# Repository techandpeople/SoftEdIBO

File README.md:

# SoftEdIBO

Soft-based robot platform for inclusive, embodied interaction.
Developed at [LASIGE](https://www.lasige.pt/), Faculdade de Ciencias, Universidade de Lisboa.

SoftEdIBO controls soft robots equipped with inflatable air chambers.
Participants interact by touching the robots, which respond through inflation and deflation.
The system supports multiple robot types (Turtle, Tree, Thymio) and activity modes.

> **Running a study?** See [SETUP.md](SETUP.md) for skin/sensor setup, magnet
> polarity, touch calibration, and the gesture-training workflow.

---

## Hardware requirements

| Component | Quantity | Notes |
|-----------|----------|-------|
| Seeed XIAO ESP32-S3 (gateway) | 1 | Connected to PC via USB; also runs a WiFi SoftAP (WiFi-OTA) + a UART link to a companion XIAO ESP32-C6 for dongle-free Thymio control |
| Seeed XIAO ESP32-C6 (Thymio RCP) | 0-1 | Optional - impersonates the Thymio RF dongle over 802.15.4 (drive wheels/LEDs/sound, no dongle). See [docs/THYMIO_WIRELESS_CONTROL.md](docs/THYMIO_WIRELESS_CONTROL.md) |
| ESP32-WROOM-32 (`node_direct`) | 1 per direct board | 3 chambers, direct ADC sensors, onboard pumps |
| ESP32-WROOM-32 (`node_multiplexed`) | 1 per multiplexed board | Up to 9 chambers: 3 skins of 3, one pump pair each (runtime configurable) |
| DRV3297 motor driver | 1 (`node_direct`) / up to 3 (`node_multiplexed`) | Drives pumps with PWM |
| Air pump | 2 (`node_direct`) / up to 6 (`node_multiplexed`) | Inflate/deflate supply - pumps push directly into the chambers |
| XGZP6847A pressure sensor | 1 per chamber | Analog output (0-3.3 V) |
| Solenoid valves | 2 per chamber | Inflate + deflate via ULN2803A |

Flash the [gateway firmware](firmware/gateway/) to the USB-connected board - one
build, a **Seeed XIAO ESP32-S3** (ESP-IDF), which does everything: ESP-NOW chamber
control + a WiFi SoftAP (for WiFi-OTA) + a UART link to a companion C6 for Thymios.
For each node, choose the matching firmware target:

| Firmware | Path | When to use |
|----------|------|-------------|
| `node_actuator` env `direct` / `direct_debug` | [firmware/node_actuator/](firmware/node_actuator/) | Direct board (fixed 3 chambers) |
| `node_actuator` env `multiplexed` / `multiplexed_debug` | [firmware/node_actuator/](firmware/node_actuator/) | Multiplexed board (default 9 chambers, runtime configurable) |
| `node_magnet_sensor` | [firmware/node_magnet_sensor/](firmware/node_magnet_sensor/) | 4x MLX90393 magnetic touch board (`node_magnet_sensor` protocol) |

---

## Architecture

```
PC --USB--> Gateway (XIAO ESP32-S3) --ESP-NOW--> node_direct      (3 chambers, direct GPIO valves + own pumps)
                                    |        +-> node_multiplexed (up to 9 chambers)
                                    +--UART--> C6 --802.15.4--> Thymio  (dongle-free wheels/LEDs/sound; optional)
```

**Software layers:**

```
SessionPanel
  +-- Activity (declarative behaviours run by ScriptedActivity)
        +-- Robot (Turtle / Tree / Thymio / Simulated)
              +-- Node(s)  (ESP32, identified by MAC + node_type + max_slots)
              +-- Skin(s)  (logical grouping of 1-3 chambers from one node of this robot)
                    +-- AirChamber  (local index 0-2, pressure 0-100 %)
```

- **Node** is a physical ESP32. Its `node_type` (`node_direct` or `node_multiplexed`) determines which firmware to flash.
- **Skin** groups 1-3 chambers, all on the same node (a skin never spans MACs). Activities address chambers by local skin index (0, 1, 2) - no knowledge of node topology required.
- **Pressure** is expressed as **0-100 %** of the maximum pressure configured on each node.
- **Per-chamber max pressure** is set in `settings.yaml` and enforced both in the app and on the ESP32 (hardware safety - survives app crashes).
- **Pressure sensing** uses the XGZP6847A datasheet transfer function (see [pressure.h](firmware/common/pressure.h)).

**Touch sensing (optional).** A skin may reference a `node_magnet_sensor` (4-sensor magnet sensor/touch board) via its `touch:` block - see [firmware/PROTOCOL.md](firmware/PROTOCOL.md). The activity-time view (`SkinGridView`) overlays a pulsing yellow outline on the active sensor cells so the operator sees where each touch lands relative to the chamber regions.

**Skin geometry by type.** Each skin sets a `skin_type` (e.g. `turtle_square`, `tree_round`, `thymio`) whose **shape and sensor coordinates** are hardcoded in [`src/hardware/skin_geometry.py`](src/hardware/skin_geometry.py). The skin dialog offers only the current robot's types and draws the real outline/aspect (square, rectangle, round, triangle, Thymio "D") - editor and activity view share the masks in [`src/gui/skin_shapes.py`](src/gui/skin_shapes.py). The legacy paint-grid editor still applies to skins without a `skin_type`.

**Sensor stream recording + touch-gesture ML.** A session can record every sensor message to `data/recordings/<id>.jsonl` (toggle in the setup dialog - no video). Those recordings, plus gestures tagged live in the observer panel, feed a **per-`skin_type`, coordinate-free** touch-gesture classifier (tap / press / compressions - `src/ml/gesture_taxonomy.py`). `scikit-learn` is the optional `ml` extra; the classifier is inert without a trained model. See [docs/TOUCH_ML.md](docs/TOUCH_ML.md).

**Activities are declarative behaviours.** No activities are hard-coded: every activity is a behaviour spec authored in the block editor (**Tools -> Activity Editor...**), stored in the DB (or imported from JSON examples in `config/examples/behaviours/`) and interpreted at session time by `ScriptedActivity`. See [docs/ACTIVITIES.md](docs/ACTIVITIES.md).

---

## Installation

### Linux (x86-64)

```bash
curl -fsSL https://raw.githubusercontent.com/techandpeople/SoftEdIBO/master/install.sh | bash
```

This will download the latest release, install it to `~/.local/opt/SoftEdIBO/`, create a `softedibo` command in `~/.local/bin/`, and add a desktop entry to the application menu.

**Nightly build** (latest commit on `master`):

```bash
curl -fsSL https://raw.githubusercontent.com/techandpeople/SoftEdIBO/master/install.sh | bash -s -- --nightly
```

**Uninstall:**

```bash
softedibo --uninstall
```

> **First time with USB?** After installing, run:
> ```bash
> sudo usermod -aG dialout $USER
> ```
> Then log out and back in. The installer does this automatically if needed.

---

### Windows (x64)

1. Download **`SoftEdIBO-windows-x64.zip`** from the [latest release](https://github.com/techandpeople/SoftEdIBO/releases/latest)
2. Extract and run **`SoftEdIBO.exe`**

> **USB driver:** install the [CH340](https://www.wch-ic.com/downloads/CH341SER_EXE.html) or [CP210x](https://www.silabs.com/developers/usb-to-uart-bridge-vcp-drivers) driver if your device is not detected.

---

## Usage

On first launch, a setup wizard guides you through flashing the firmware to the ESP32 nodes.

### Configuration (`settings.yaml`)

The app reads and writes the **user copy** of the settings file:
`~/.local/share/SoftEdIBO/config/settings.yaml` on Linux,
`%APPDATA%\SoftEdIBO\config\settings.yaml` on Windows. On first run it is copied
from the bundled default, the repo's [config/settings.yaml](config/settings.yaml);
later edits to the repo file do not reach an existing user copy.

Robots are configured per type (`turtles:` / `trees:` / `thymios:`), each with its own `nodes:` (ESP32s by MAC) and `skins:` on top. A skin lists its chambers - each a `{mac, slot}` pair on a single node - with optional per-chamber `max_pressure` / `min_pressure` safety limits in kPa. It is all editable from the GUI (Robots panel); the commented examples in [config/settings.yaml](config/settings.yaml) show the full shape (skin types, touch blocks, Thymio entries).

```yaml
robots:
  turtles:
    - id: turtle_1
      nodes:
        - mac: "AA:BB:CC:DD:EE:01"
          node_type: "node_multiplexed"
          max_slots: 12
      skins:
        - skin_id: shell_top
          name: Shell Top
          skin_type: turtle_square
          chambers:
            - {mac: "AA:BB:CC:DD:EE:01", slot: 0, max_pressure: 8.0}
            - {mac: "AA:BB:CC:DD:EE:01", slot: 1, max_pressure: 6.0}
  trees: []
  thymios: []
```

- Multiple skins can share the same node MAC; each skin groups up to 3 of that node's slots.
- `max_pressure` is sent to the ESP32 node on startup as kPa. The gateway forwards it unchanged; the node enforces it independently - even if the app crashes, chambers will not exceed their configured limit.
- If `max_pressure` / `min_pressure` are omitted, chambers default to 30 kPa / -5 kPa.

---

## Development

### Python application

```bash
# Qt platform libs (Debian/Ubuntu). Without libxcb-cursor0 the app aborts with
# "Could not load the Qt platform plugin xcb" - the app forces xcb (see run.py).
# libxkbfile1 is needed by QtWebEngine (the activity editor crashes without it).
sudo apt-get install -y libgl1 libegl1 libglib2.0-0 libdbus-1-3 \
  libxcb1 libxcb-cursor0 libxcb-icccm4 libxcb-image0 libxcb-keysyms1 \
  libxcb-randr0 libxcb-render-util0 libxcb-shape0 libxcb-xinerama0 \
  libxcb-xkb1 libxkbcommon-x11-0 libfontconfig1 libxkbfile1

git clone https://github.com/techandpeople/SoftEdIBO.git
cd SoftEdIBO
python -m venv .venv && source .venv/bin/activate
pip install -r requirements.txt
./scripts/compile_ui.sh     # generates src/gui/ui_*.py - not in git
python scripts/run.py
```

Or with the Makefile: `make install && make run` (`make` alone lists every
target - tests, type check, firmware build/flash/monitor, PyInstaller bundle).
`make run` recompiles only the changed `.ui` files on its own.

Requires Python 3.12+. Re-run `./scripts/compile_ui.sh` after editing any
`src/gui/ui/*.ui` file, or the app fails with
`ModuleNotFoundError: No module named 'src.gui.ui_...'`.

**Debug mode** - shows all log levels on the console (DEBUG+):

```bash
python scripts/run.py --debug
```

Without `--debug`, only warnings and errors are shown on the console. All log
levels are always written to `softedibo.log` in the per-user state directory
(`~/.local/state/SoftEdIBO/` on Linux, `%LOCALAPPDATA%\SoftEdIBO\` on Windows;
rotating, 2 MB x 3 backups).

### Firmware

```bash
# Gateway - one build, Seeed XIAO ESP32-S3 (ESP-IDF)
cd firmware/gateway && pio run -e seeed_xiao_esp32s3 --target upload

# Actuator nodes (one project, env per variant)
cd firmware/node_actuator && pio run -e direct      --target upload
cd firmware/node_actuator && pio run -e multiplexed --target upload

# Sensor node (4x MLX90393 touch board)
cd firmware/node_magnet_sensor && pio run -e release --target upload

# Thymio radio co-processor (optional) - Seeed XIAO ESP32-C6
cd firmware/thymio_rcp && pio run -e rcp_c6 --target upload
```

Prebuilt binaries for all of the above are produced by `scripts/build-firmware.sh`.

Requires [PlatformIO](https://platformio.org/).

> **Updating nodes later:** once a node has been cable-flashed once with the
> current partition table, you can reflash it wirelessly via **Tools -> Update
> Nodes (OTA)...** in the app - it streams the bundled firmware to the node over
> ESP-NOW through the connected gateway (no cable, no WiFi). See
> [firmware/gateway/README.md](firmware/gateway/README.md#ota-firmware-update-over-esp-now).

CI builds **every** firmware variant on each run (release + debug, RGB + RGBW)
and ships them all - bundled in the app and in `firmware.zip` - for both the
nightly pre-release (push to `master`) and stable releases (tag `v*`). The debug
build is picked at flash time with the **Debug build** checkbox in the setup
wizard / **Tools -> Update Nodes (OTA)...**.

### Debug builds

| Layer | Production | Development |
|-------|-----------|-------------|
| **Python app** | `run.py` - warnings only on console | `run.py --debug` - all levels on console |
| **Node firmware** | `release` env - no Serial, no debug overhead | `debug` env - Serial logs, tx counters, `{"cmd":"debug"}` |
| **Gateway firmware** | Single build, no debug overhead | Same (transparent bridge, nothing to gate) |

### Key source paths

| Path | Description |
|------|-------------|
| `src/hardware/skin.py` | Skin model - groups 1-3 AirChambers on one ESP32 node; `skin_type` + `geometry` |
| `src/hardware/skin_geometry.py` | Hardcoded skin-geometry registry (shape + sensor coords) keyed by `skin_type` |
| `src/hardware/air_chamber.py` | AirChamber model - pressure 0-100 %, configurable max |
| `src/hardware/esp32_controller.py` | Real hardware controller (via the SoftEdIBO gateway) |
| `src/hardware/simulated_controller.py` | Mock controller for simulation mode |
| `src/hardware/touch_profiles.py` | Touch-sensor technology seam (magnet today, capacitive skeleton) - see [docs/TOUCH_SENSORS.md](docs/TOUCH_SENSORS.md) |
| `src/data/stream_recorder.py` | Per-session JSONL recorder of all gateway sensor messages |
| `src/data/export.py` | Session CSV export with robot/participant attribution |
| `src/ml/` | Touch-gesture pipeline (segmenter, features, classifier) - see [docs/TOUCH_ML.md](docs/TOUCH_ML.md) |
| `src/gui/skin_shapes.py` | Shared skin-outline masks (round/triangle/thymio) + aspect ratio |
| `src/robots/` | TurtleRobot, TreeRobot, ThymioRobot, SimulatedRobot |
| `src/activities/` | Activity registry + declarative behaviour engine (`ScriptedActivity`, verb catalogue) |
| `src/gui/monitor/` | Live pressure monitor widgets |
| `scripts/label_touches.py` / `scripts/train_touch_model.py` | Offline touch-gesture labelling + training (`.[ml]` extra) |
| `src/log.py` | Centralized logging setup (console + rotating file) |
| `config/settings.yaml` | Default robot and hardware configuration (copied to the user data dir on first run) |
| `firmware/gateway/` | Gateway firmware (ESP-IDF, Seeed XIAO ESP32-S3) |
| `firmware/thymio_rcp/` | Thymio radio co-processor (XIAO ESP32-C6) - dongle-free 802.15.4 control; see [docs/THYMIO_WIRELESS_CONTROL.md](docs/THYMIO_WIRELESS_CONTROL.md) |
| `firmware/common/` | Shared firmware headers (`se_espnow.h`, units/pressure/dbg/cmd_queue) |
| `firmware/node_actuator/` | Actuator nodes - `direct` + `multiplexed` variants (build-flag envs) |
| `firmware/node_magnet_sensor/` | Sensor node - 4x MLX90393 touch board (`node_magnet_sensor` protocol) |
| `firmware/node_actuator/src/direct/pins.h` | node_direct pin definitions |
| `firmware/node_actuator/src/multiplexed/pins.h` | node_multiplexed pin definitions |

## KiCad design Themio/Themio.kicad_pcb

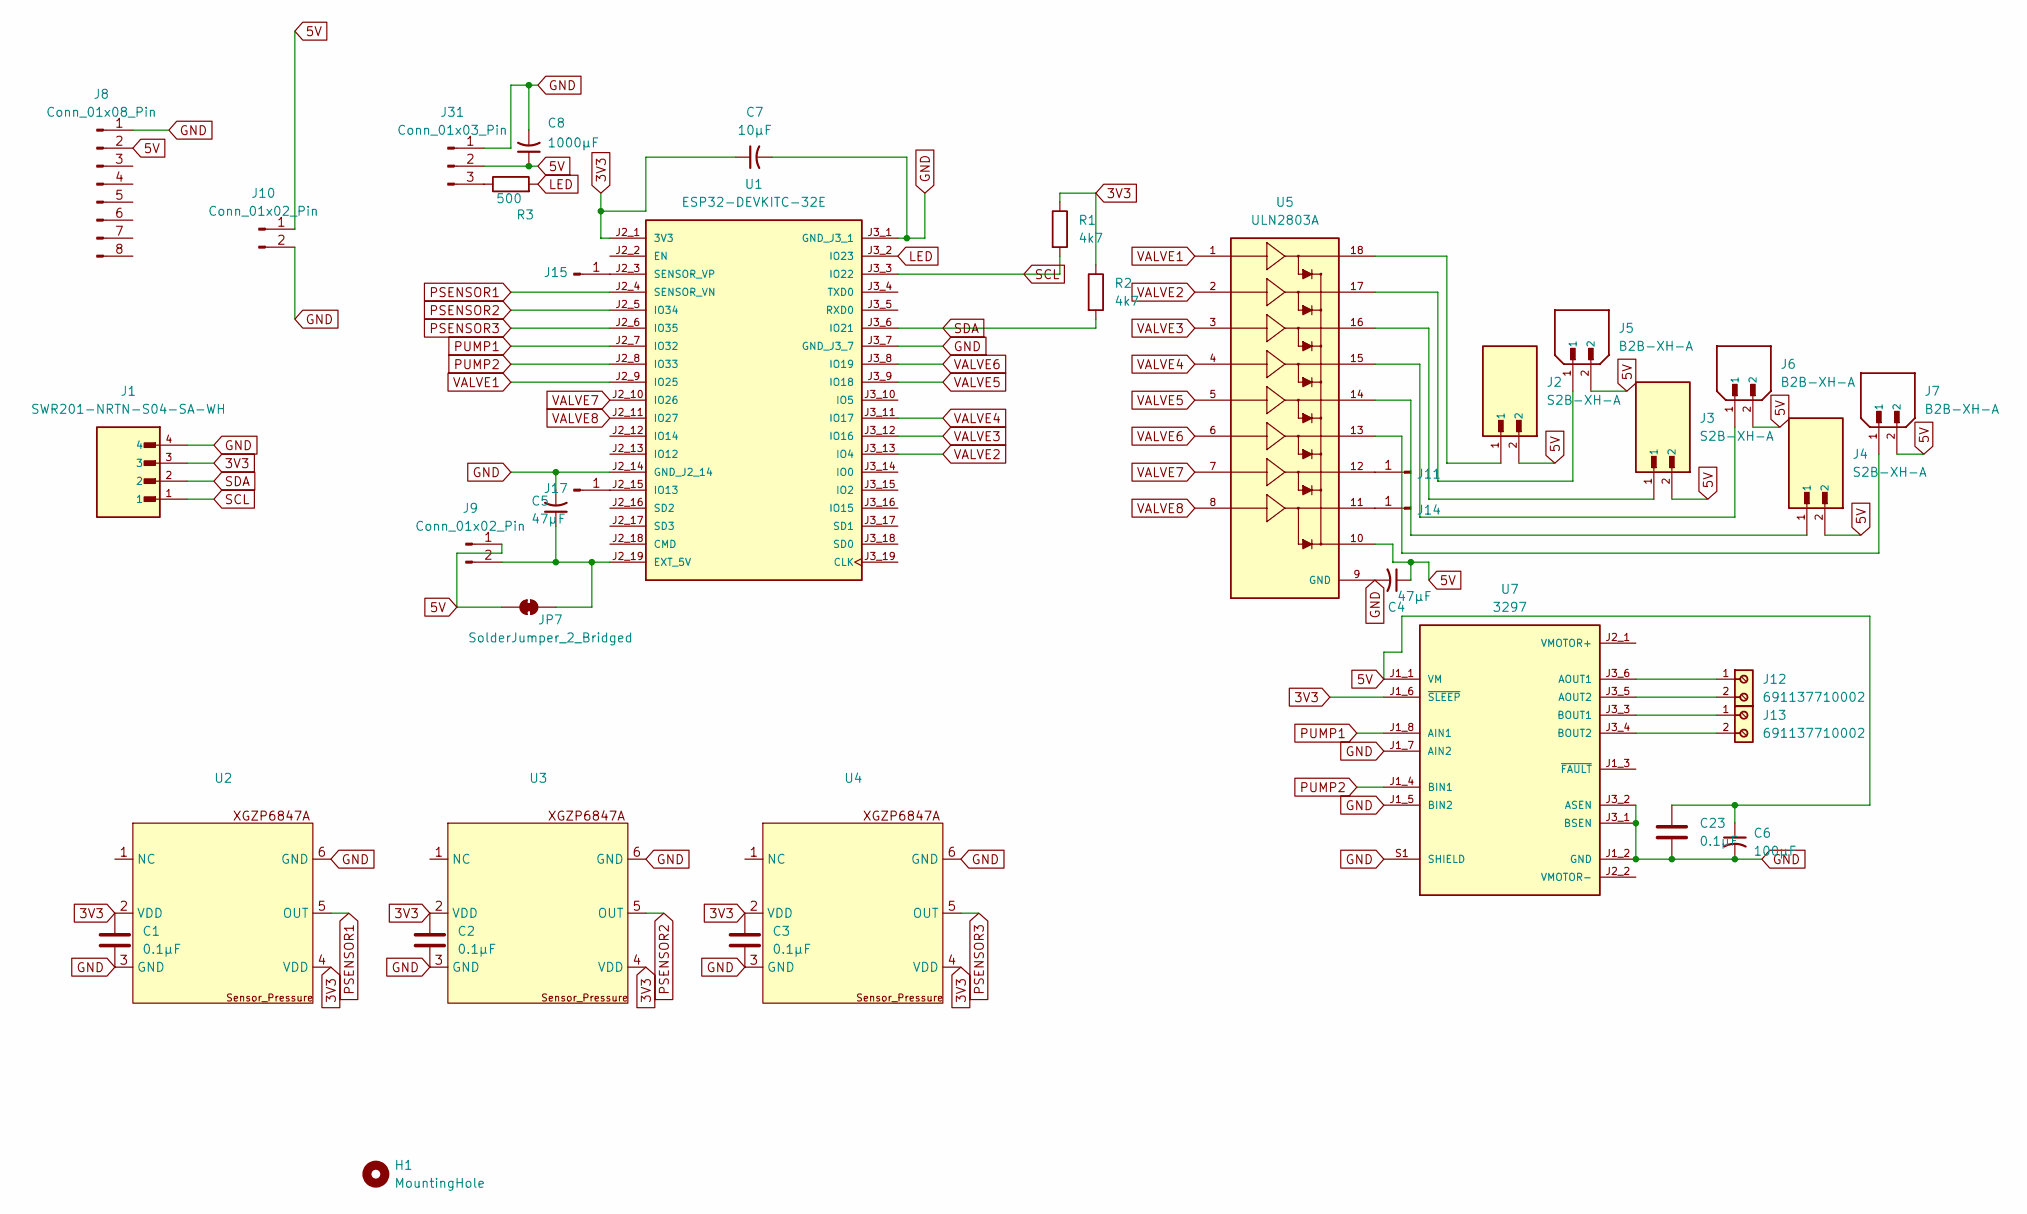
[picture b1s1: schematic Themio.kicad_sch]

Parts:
C1, C2, C3, C23: 0.1µF; C_Disc_D5.0mm_W2.5mm_P5.00mm
C4, C5: 47µF; CP_Radial_D5.0mm_P2.00mm
C6: 100µF; CP_Radial_D5.0mm_P2.00mm
C7: 10µF; CP_Radial_D5.0mm_P2.00mm
C8: 1000µF; CP_Radial_D5.0mm_P2.00mm
H1: MountingHole; MountingHole_4.3mm_M4
J1: SWR201-NRTN-S04-SA-WH; SULLINS_SWR201-NRTN-S04-SA-WH; PARTREV A
J2, J3, J4: S2B-XH-A; JST_S2B-XH-A
J5, J6, J7: B2B-XH-A; JST_B2B-XH-A; PARTREV N/A
J8: Conn_01x08_Pin; PinHeader_1x08_P2.54mm_Vertical
J9, J10: Conn_01x02_Pin; PinHeader_1x02_P2.54mm_Vertical
J11, J14, J15, J17: Conn_01x01_Pin; PinHeader_1x01_P2.54mm_Vertical
J12, J13: 691137710002
J31: Conn_01x03_Pin; PinHeader_1x03_P2.54mm_Vertical
JP7: SolderJumper_2_Bridged; SolderJumper-2_P1.3mm_Bridged_RoundedPad1.0x1.5mm
R1, R2: 4k7; R_Axial_DIN0207_L6.3mm_D2.5mm_P7.62mm_Horizontal
R3: 500; R_Axial_DIN0207_L6.3mm_D2.5mm_P7.62mm_Horizontal
U1: ESP32-DEVKITC-32E; MODULE_ESP32-DEVKITC-32E; PARTREV 1.4
U2, U3, U4: XGP6847A_TiagoDias
U5: ULN2803A; UNL; PARTREV 4
U7: 3297; MODULE_3297; PARTREV 2020-11-20

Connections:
3V3: C1.1, C2.1, C3.1, C7.1, J1.3, R1.1, R2.1, U1.J2_1 (3V3), U2.2 (VDD), U2.4 (VDD), U3.2 (VDD), U3.4 (VDD), U4.2 (VDD), U4.4 (VDD), U7.J1_6 (~SLEEP)
5V: C4.1, C6.1, C8.1, C23.1, J2.2, J3.2, J4.2, J5.2, J6.2, J7.2, J8.2, J9.1, J10.1, J31.2, JP7.1 (A), U5.10, U7.J1_1 (VM)
GND: C1.2, C2.2, C3.2, C4.2, C5.2, C6.2, C7.2, C8.2, C23.2, J1.4, J8.1, J10.2, J31.1, U1.J2_14 (GND_J2_14), U1.J3_1 (GND_J3_1), U1.J3_7 (GND_J3_7), U2.3 (GND), U2.6 (GND), U3.3 (GND), U3.6 (GND), U4.3 (GND), U4.6 (GND), U5.9 (GND), U7.J1_2 (GND), U7.J1_5 (BIN2), U7.J1_7 (AIN2), U7.J3_1 (BSEN), U7.J3_2 (ASEN), U7.S1 (SHIELD), U7.S2 (SHIELD)
LED: R3.2, U1.J3_2 (IO23)
unnamed: J2.1, U5.18
unnamed: J3.1, U5.16
unnamed: J4.1, U5.14
unnamed: J5.1, U5.17
unnamed: J6.1, U5.15
unnamed: J7.1, U5.13
unnamed: C5.1, J9.2, JP7.2 (B), U1.J2_19 (EXT_5V)
unnamed: J11.1, U5.12
unnamed: J14.1, U5.11
unnamed: J15.1, U1.J2_3 (SENSOR_VP)
unnamed: J17.1, U1.J2_15 (IO13)
unnamed: J31.3, R3.1
unnamed: J12.1, U7.J3_6 (AOUT1)
unnamed: J12.2, U7.J3_5 (AOUT2)
unnamed: J13.1, U7.J3_3 (BOUT1)
unnamed: J13.2, U7.J3_4 (BOUT2)
PSENSOR1: U1.J2_4 (SENSOR_VN), U2.5 (OUT)
PSENSOR2: U1.J2_5 (IO34), U3.5 (OUT)
PSENSOR3: U1.J2_6 (IO35), U4.5 (OUT)
PUMP1: U1.J2_7 (IO32), U7.J1_8 (AIN1)
PUMP2: U1.J2_8 (IO33), U7.J1_4 (BIN1)
SCL: J1.1, R1.2, U1.J3_3 (IO22)
SDA: J1.2, R2.2, U1.J3_6 (IO21)
VALVE1: U1.J2_9 (IO25), U5.1
VALVE2: U1.J3_13 (IO4), U5.2
VALVE3: U1.J3_12 (IO16), U5.3
VALVE4: U1.J3_11 (IO17), U5.4
VALVE5: U1.J3_9 (IO18), U5.5
VALVE6: U1.J3_8 (IO19), U5.6
VALVE7: U1.J2_10 (IO26), U5.7
VALVE8: U1.J2_11 (IO27), U5.8

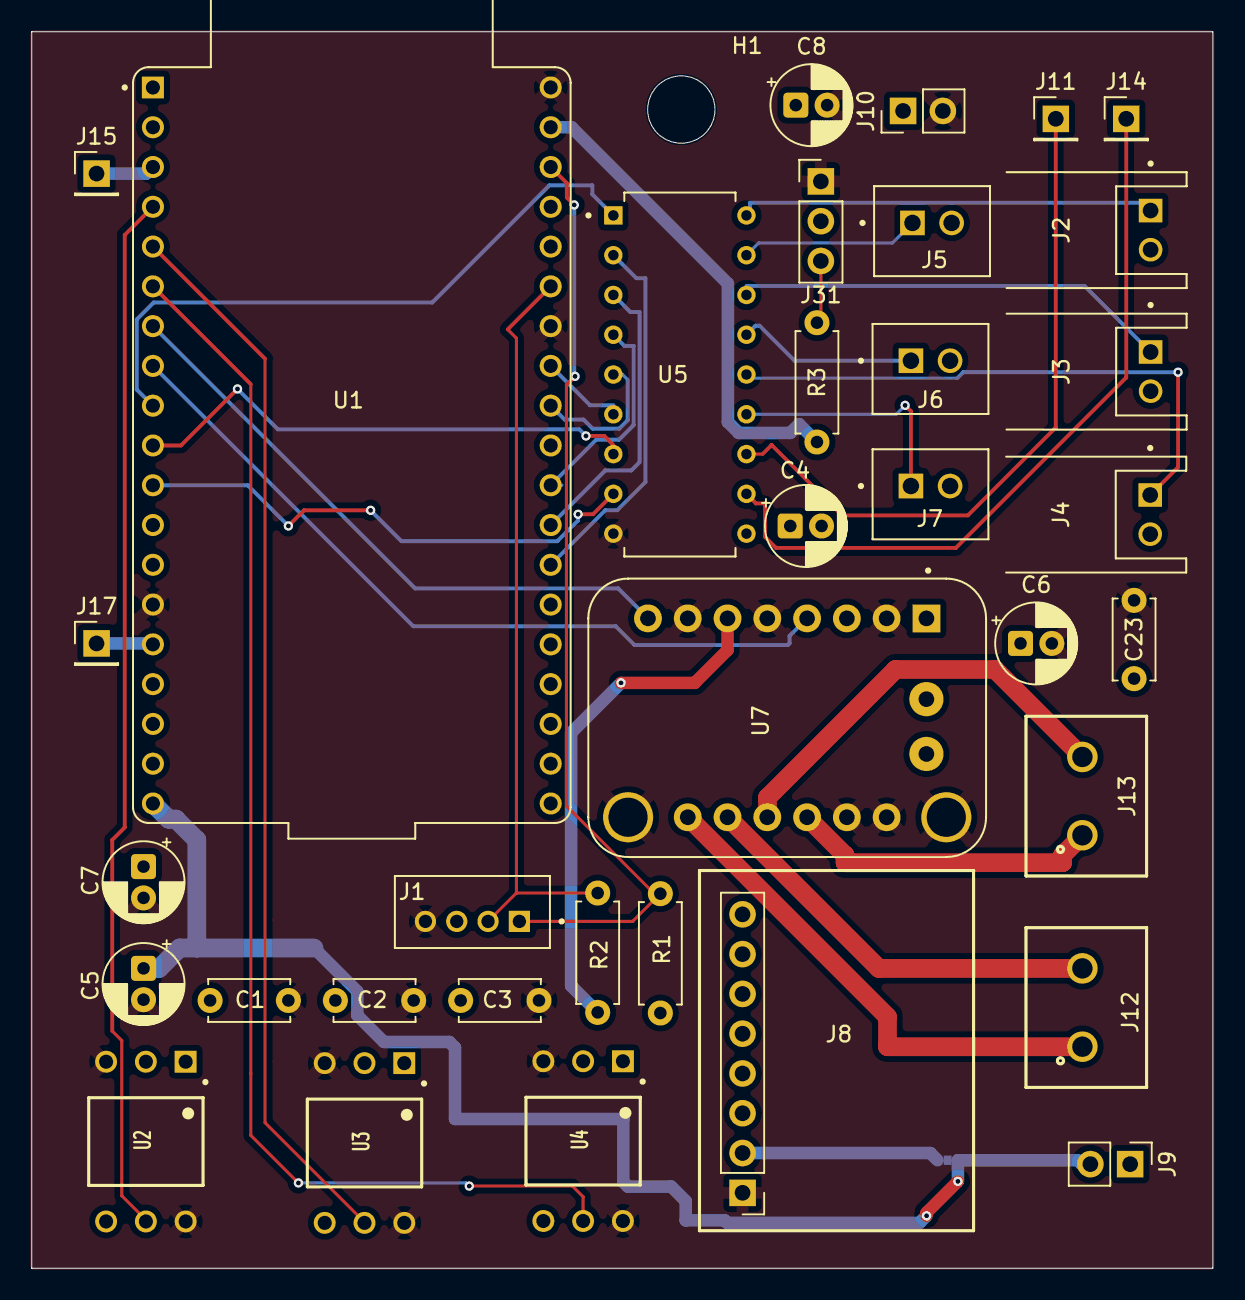
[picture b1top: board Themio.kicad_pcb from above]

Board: 4 copper layers, 75.4 x 79.0 mm, 37 parts (1 on the bottom side), 35 nets.

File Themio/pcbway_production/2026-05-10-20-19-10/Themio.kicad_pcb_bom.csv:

Designator,Quantity,Value,Footprint,Package,MPN,DNP,Mount_Type,Description,MF,MAXIMUM_PACKAGE_HEIGHT,Price,Check_prices,STANDARD,PARTREV,SnapEDA_Link,MP,Description_1,Availability,MANUFACTURER,Purchase-URL
"C1, C2, C23, C3",4,0.1µF,C_Disc_D5.0mm_W2.5mm_P5.00mm,,,,tht,Unpolarized capacitor,,,,,,,,,,,,
"C4, C5",2,47µF,CP_Radial_D5.0mm_P2.00mm,,,,tht,"capacitor, small US symbol",,,,,,,,,,,,
C6,1,100µF,CP_Radial_D5.0mm_P2.00mm,,,,tht,"capacitor, small US symbol",,,,,,,,,,,,
C7,1,10µF,CP_Radial_D5.0mm_P2.00mm,,,,tht,"capacitor, small US symbol",,,,,,,,,,,,
C8,1,1000µF,CP_Radial_D5.0mm_P2.00mm,,,,tht,"capacitor, small US symbol",,,,,,,,,,,,
J1,1,SWR201-NRTN-S04-SA-WH,SULLINS_SWR201-NRTN-S04-SA-WH,None,,,tht,,Sullins Connector Solutions,6.00mm,None,https://www.snapeda.com/parts/SWR201-NRTN-S04-SA-WH/Sullins/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,Manufacturer Recommendations,A,https://www.snapeda.com/parts/SWR201-NRTN-S04-SA-WH/Sullins/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,SWR201-NRTN-S04-SA-WH,Connector Header Through Hole 4 position 0.079 (2.00mm),In Stock,Sullins,
"J10, J9",2,Conn_01x02_Pin,PinHeader_1x02_P2.54mm_Vertical,,,,tht,"Generic connector, single row, 01x02, script generated",,,,,,,,,,,,
"J11, J14, J15, J17",4,Conn_01x01_Pin,PinHeader_1x01_P2.54mm_Vertical,,,,tht,"Generic connector, single row, 01x01, script generated",,,,,,,,,,,,
"J12, J13",2,691137710002,691137710002,None,,,tht,,Würth Elektronik,,None,https://www.snapeda.com/parts/691137710002/W%25C3%25BCrth+El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,,,https://www.snapeda.com/parts/691137710002/W%25C3%25BCrth+El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,691137710002,2 Position Wire to Board Terminal Block Horizontal with Board 0.197 (5.00mm) Through Hole,In Stock,,https://www.snapeda.com/api/url_track_click_mouser/?unipart_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 Elektronik&part_name=691137710002&search_term=691137710002
"J2, J3, J4",3,S2B-XH-A,JST_S2B-XH-A,None,,,tht,,JST Sales,,None,https://www.snapeda.com/parts/S2B-XH-A/JST/view-part/?ref=eda,,,https://www.snapeda.com/parts/S2B-XH-A/JST/view-part/?ref=snap,S2B-XH-A,"Connector Header Through Hole, Right Angle 2 position 0.098 (2.50mm)",In Stock,JST,https://www.snapeda.com/api/url_track_click_mouser/?unipart_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 Sales&part_name=S2B-XH-A&search_term=conector s2b-xh-a
J31,1,Conn_01x03_Pin,PinHeader_1x03_P2.54mm_Vertical,,,,tht,"Generic connector, single row, 01x03, script generated",,,,,,,,,,,,
"J5, J6, J7",3,B2B-XH-A,JST_B2B-XH-A,None,,,tht,,JST Sales,7 mm,None,https://www.snapeda.com/parts/B2B-XH-A/JST/view-part/?ref=eda,Manufacturer Recommendations,N/A,https://www.snapeda.com/parts/B2B-XH-A/JST/view-part/?ref=snap,B2B-XH-A,Connector Header Through Hole 2 position 0.098 (2.50mm),In Stock,JST Sales America Inc.,https://www.snapeda.com/api/url_track_click_mouser/?unipart_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 Sales&part_name=B2B-XH-A&search_term=b2b-xh-a
J8,1,Conn_01x08_Pin,PinHeader_1x08_P2.54mm_Vertical,,,,tht,"Generic connector, single row, 01x08, script generated",,,,,,,,,,,,
"R1, R2",2,4k7,R_Axial_DIN0207_L6.3mm_D2.5mm_P7.62mm_Horizontal,,,,tht,Resistor,,,,,,,,,,,,
R3,1,500,R_Axial_DIN0207_L6.3mm_D2.5mm_P7.62mm_Horizontal,,,,tht,Resistor,,,,,,,,,,,,
U1,1,ESP32-DEVKITC-32E,MODULE_ESP32-DEVKITC-32E,None,,,tht,,Espressif Systems,,None,https://www.snapeda.com/parts/ESP32-DEVKITC-32E/Espressif+Sy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,Manufacturer Recommendations,1.4,https://www.snapeda.com/parts/ESP32-DEVKITC-32E/Espressif+Sy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,ESP32-DEVKITC-32E,"The ESP32-DEVKITC-32E transceiver evaluation board from Espressif Systems is a powerful development tool for wireless communication technologies. It supports 802.11 b/g/n Wi-Fi and Bluetooth® Smart Ready 4.x (BLE) dual-mode at 2.4GHz, making it ideal for a variety of IoT applications. Equipped with a PCB antenna and 4MB flash, this board provides reliable connectivity and ample memory for developing and testing RF, RFID, and wireless solutions.",In Stock,Espressif Systems,https://www.snapeda.com/api/url_track_click_mouser/?unipart_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 Systems&part_name=ESP32-DEVKITC-32E&search_term=esp32
"U2, U3, U4",3,~,XGP6847A_TiagoDias,,,,tht,,,,,,,,,,,,,
U5,1,ULN2803A,UNL,DIP-18 Allegro MicroSystems LLC,,,tht,,STMicroelectronics,3.93mm,None,https://www.snapeda.com/parts/ULN2803A/STMicroelectronics/vi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,IPC-7351B,4,https://www.snapeda.com/parts/ULN2803A/STMicroelectronics/vi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,ULN2803A,Bipolar (BJT) Transistor Array 8 NPN Darlington 50V 500mA - 2.25W Through Hole 18-DIP,In Stock,STMicroelectronics,https://www.snapeda.com/api/url_track_click_mouser/?unipart_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
U7,1,3297,MODULE_3297,None,,,tht,,Adafruit Industries,NA,None,https://www.snapeda.com/parts/3297/Adafruit+Industries/view-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,Manufacturer Recommendations,2020-11-20,https://www.snapeda.com/parts/3297/Adafruit+Industries/view-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,3297,DRV8833 - Motor Controller/Driver Power Management Evaluation Board,In Stock,Adafruit,

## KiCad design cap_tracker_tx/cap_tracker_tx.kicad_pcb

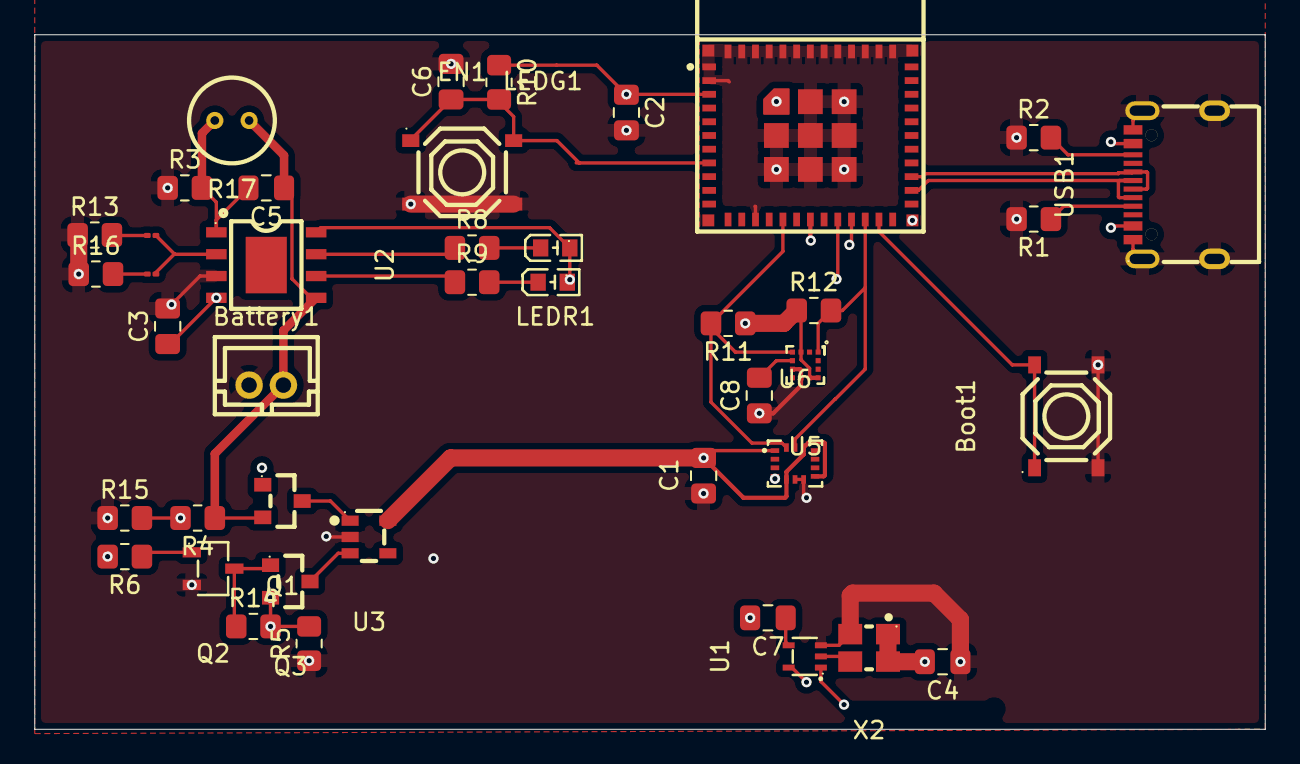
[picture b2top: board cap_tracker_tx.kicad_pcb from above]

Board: 4 copper layers, 71.8 x 40.5 mm, 43 parts (1 on the bottom side), 30 nets.

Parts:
Battery1: B2B-PH-K-S; CONN-TH_B2B-PH-K-S
Boot1: TS-1187A-B-A-B; SW-SMD_4P-L5.1-W5.1-P3.70-LS6.5-TL_H1.5
C1, C2, C4, C7: 100 nF; C_0805_2012Metric_Pad1.18x1.45mm_HandSolder
C3, C5: 10 uF; C_0805_2012Metric_Pad1.18x1.45mm_HandSolder
C6: 1 uF; C_0805_2012Metric_Pad1.18x1.45mm_HandSolder
C8: 220 nF; C_0805_2012Metric_Pad1.18x1.45mm_HandSolder
CN1: YZ182615065D-01; SMD-1_BD2.0-D1.0
EN1: TS-1187A-B-A-B; SW-SMD_4P-L5.1-W5.1-P3.70-LS6.5-TL_H1.5
JP1, JP2: Jumper_2_Small_Bridged; MouseBite-Slot-Jumper_01005
LEDG1: YLED0603G; LED0603-FD
LEDR1: YLED0603R; LED0603-FD
Q1, Q3: AO3401A_C347476; SOT-23_L2.9-W1.3-P1.90-LS2.4-BR
Q2: MMBT3904LT1G; SOT-23-3_L2.9-W1.6-P1.90-LS2.8-BR
R1, R2: 5.1k; R_0805_2012Metric_Pad1.20x1.40mm_HandSolder
R3, R4, R5, R14, R15: 100K; R_0805_2012Metric_Pad1.20x1.40mm_HandSolder
R6, R10: 10K; R_0805_2012Metric_Pad1.20x1.40mm_HandSolder
R8: 1K; R_0805_2012Metric_Pad1.20x1.40mm_HandSolder
R9: 470; R_0805_2012Metric_Pad1.20x1.40mm_HandSolder
R11, R12: 2.2K; R_0805_2012Metric_Pad1.20x1.40mm_HandSolder
R13: 2.4K; R_0805_2012Metric_Pad1.20x1.40mm_HandSolder
R16: 1.2K; R_0805_2012Metric_Pad1.20x1.40mm_HandSolder
R17: HNTC-103F3950FB; RES-TH_BD2.5-P2.0_HNTC-103F3950FB
U1: 74LVC1G08GW_C52140431; SOT-353-5_L2.1-W1.3-P0.65-LS2.3-BL
U2: TP4056; ESOP-8_L4.9-W3.9-P1.27-LS6.0-BL-EP
U3: AP2112K-3.3TRG1_C23380830; SOT-23-5_L2.9-W1.6-P0.95-LS2.8-BR
U4: ESP32-C3-MINI-1-N4; WIFIM-SMD_ESP32-C3-MINI-1
U5: LIS2MDLTR; VLGA-12_L2.0-W2.0-P0.50-BL
U6: LSM6DSOXTR; LGA-14L_L3.0-W2.5-P0.50-TL
USB1: TYPE-C 16PIN 2MD; USB-C-SMD_TYPE-C-16PIN-2MD-073
X2: SX3M13.560B10F20TNN; OSC-SMD_4P-L3.2-W2.5-BL-1

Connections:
+3.3V: C1.2, C2.1, R10.1, R11.1, R12.1, U3.5 (VOUT), U4.3 (3V3), U5.3 (CS), U5.9 (Vdd), U5.10 (Vdd_IO), U6.1 (SDO/SA0), U6.5 (VDDIO), U6.8 (VDD), U6.12 (CS)
/ENIG Surface: C7.2, CN1.1 (1_1)
Batt Level: R4.2, R15.2, U4.18 (IO4)
Boot: Boot1.1 (A), Boot1.2 (B), U4.23 (IO9)
Dn: U4.26 (IO18), USB1.A7 (Dn1), USB1.B7 (Dn2)
Dp: U4.27 (IO19), USB1.A6 (Dp1), USB1.B6 (Dp2)
EN: C6.1, EN1.1 (A), EN1.2 (B), R10.2, U4.8 (EN)
GND: Battery1.2, Boot1.3 (C), Boot1.4 (D), C1.1, C2.2, C3.2, C4.1, C6.2, C8.1, EN1.3 (C), EN1.4 (D), Q2.2, R1.2, R2.1, R3.1, R5.1, R13.1, R15.1, R16.1, U1.3 (GND), U2.3 (GND), U3.2 (GND), U4.1 (GND), U4.2 (GND), U4.14 (GND), U4.36 (GND), U4.37 (GND), U4.38 (GND), U4.39 (GND), U4.40 (GND), U4.41 (GND), U4.42 (GND), U4.43 (GND), U4.44 (GND), U4.45 (GND), U4.46 (GND), U4.47 (GND), U4.48 (GND), U4.49 (GND), U4.50 (GND), U4.51 (GND), U4.52 (GND), U4.53 (GND), U5.6 (GND), U5.8 (GND), U6.6 (GND), U6.7 (GND), USB1.13 (EH), USB1.14 (EH), USB1.A1B12 (GND), USB1.B1A12 (GND), X2.2 (GND)
IBC Carrier: U1.2 (A), X2.3 (OUTPUT)
IBC Modulation: U1.1 (B), U4.21 (IO7)
IMU Interrupt: U4.20 (IO6), U6.4 (INT1)
LDO Input: Q1.3 (D), Q3.3 (D), U3.1 (VIN), U3.3 (EN)
unnamed: JP1.1 (A), R13.2
unnamed: JP1.2 (B), JP2.2 (B), U2.2 (PROG)
unnamed: JP2.1 (A), R16.2
unnamed: LEDG1.2 (-), R9.2
unnamed: LEDR1.2 (-), R8.2
unnamed: Battery1.1, C5.1, Q1.2 (S), R4.1, R17.1, U2.5 (BAT)
unnamed: Q2.1, R6.1
unnamed: Q2.3, Q3.1 (G), R14.1
unnamed: C7.1, U1.4 (Y)
unnamed: C5.2, R3.2, R17.2, U2.1 (TEMP)
unnamed: R8.1, U2.7 (~CHRG)
unnamed: R9.1, U2.6 (~STDBY)
unnamed: C8.2, U5.5 (C1)
unnamed: R1.1, USB1.A5 (CC1)
unnamed: R2.2, USB1.B5 (CC2)
SCL: R12.2, U4.22 (IO8), U5.1 (SCL/SPC), U6.13 (SCL)
SDA: R11.2, U4.16 (IO10), U5.4 (SDA/SDI/SDO), U6.14 (SDA)
USB 5V: C3.1, C4.2, LEDG1.1 (+), LEDR1.1 (+), Q1.1 (G), Q3.2 (S), R5.2, R6.2, R14.2, U1.5 (VCC), U2.4 (VCC), U2.8 (CE), USB1.A4B9 (VBUS), USB1.B4A9 (VBUS), X2.1 (Tri-State), X2.4 (VDD)

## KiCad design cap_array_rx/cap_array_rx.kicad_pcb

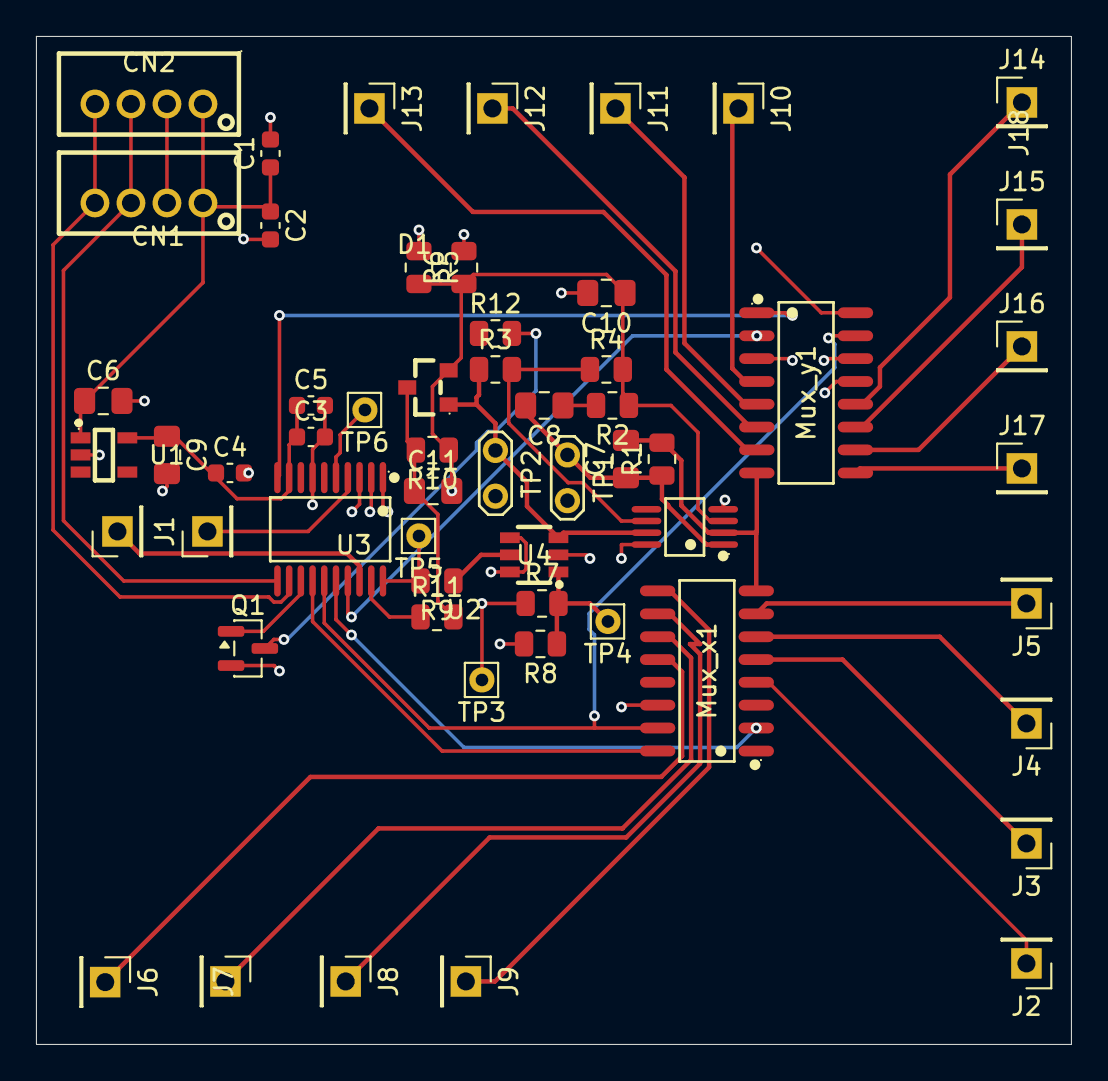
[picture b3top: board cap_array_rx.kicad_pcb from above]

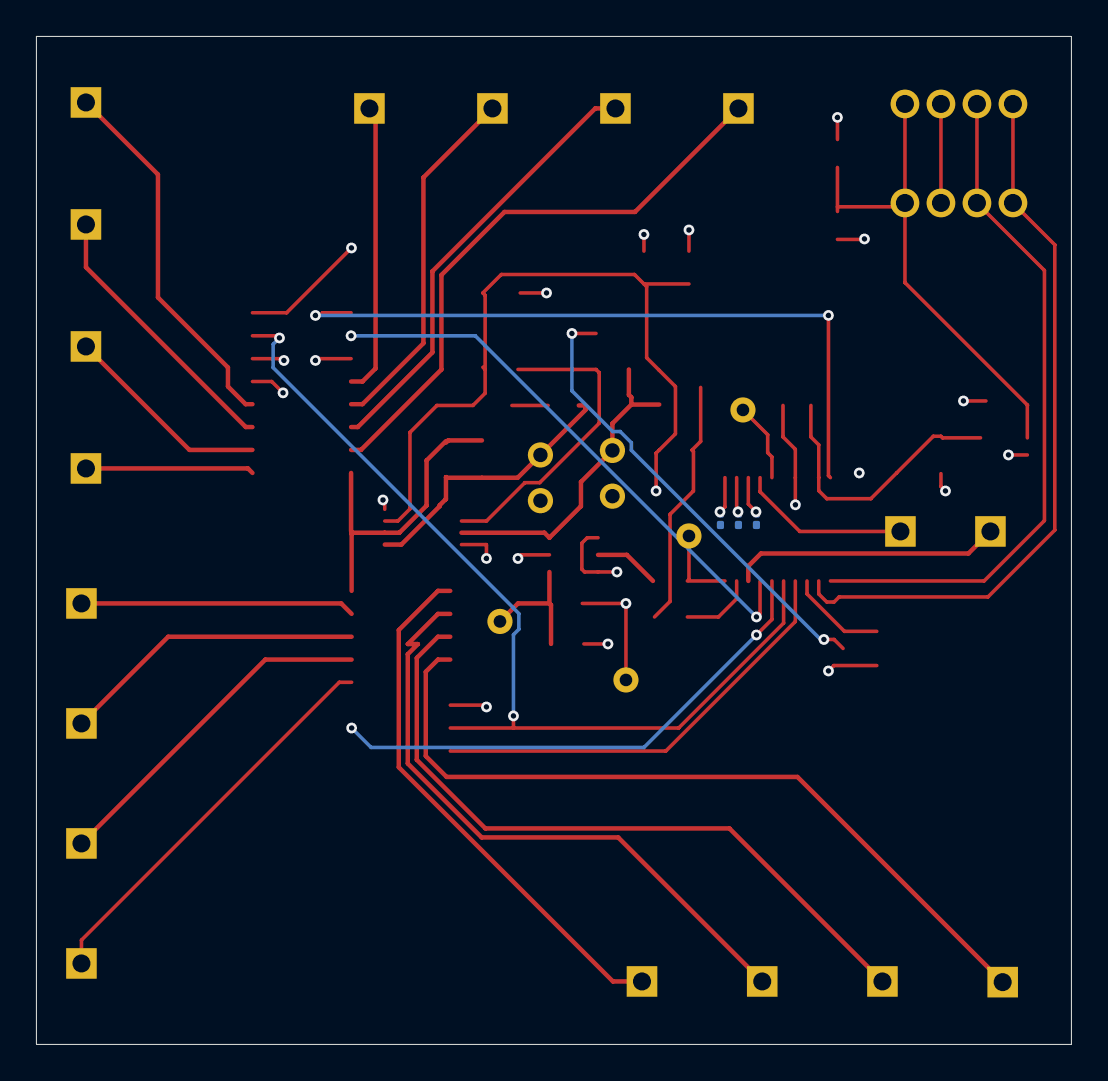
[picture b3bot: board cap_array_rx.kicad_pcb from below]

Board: 4 copper layers, 57.5 x 56.0 mm, 60 parts (3 on the bottom side), 45 nets.

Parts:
C1, C2, C3, C4, C5: 100 nF; C_0603_1608Metric
C6, C9: 10 uF; C_0805_2012Metric_Pad1.18x1.45mm_HandSolder
C7: 1.5 pF; C_0805_2012Metric_Pad1.18x1.45mm_HandSolder
C8: 1000 pF; C_0805_2012Metric_Pad1.18x1.45mm_HandSolder
C10: 100 nF; C_0805_2012Metric_Pad1.18x1.45mm_HandSolder
C11: 1 nF; C_0805_2012Metric_Pad1.18x1.45mm_HandSolder
CN1, CN2: B4B-PH-K-S; CONN-TH_B4B-PH-K-S
D1: BAT54SLT1G; SOT-23_L2.9-W1.3-P1.90-LS2.4-BR
J1: NRST; PinHeader_1x01_P2.54mm_Vertical
J2, J3, J4, J5, J6, J7, J8, J9, J10, J11, J12, J13, J14, J15, J16, J17: Conn_01x01; PinHeader_1x01_P2.54mm_Vertical
J18: SWIO; PinHeader_1x01_P2.54mm_Vertical
JP1, JP2, JP3: Jumper_2_Small_Bridged; MouseBite-Slot-Jumper_0201
Mux_x1: MUX508IDR; SOIC-16_L9.9-W3.9-P1.27-LS6.0-BL
Mux_y1: MUX508IDR; SOIC-16_L9.9-W3.9-P1.27-LS6.0-BL
Q1: 2N7002; SOT-23
R1, R3: 10 k; R_0805_2012Metric
R2, R8: 100 k; R_0805_2012Metric
R4, R12: 1 k; R_0805_2012Metric
R5, R6: 10 K; R_0805_2012Metric
R7: 620; R_0805_2012Metric
R9, R11: 200; R_0805_2012Metric
R10: 1k; R_0805_2012Metric
TP1, TP2: TestPoint_2Pole; TestPoint_2Pads_Pitch2.54mm_Drill0.8mm
TP3, TP4, TP5, TP6: TestPoint; Pin_D0.7mm_L6.5mm_W1.8mm_FlatFork
U1: AP2112K-3.3TRG1; SOT-25-5_L2.9-W1.6-P0.95-LS2.8-BL
U2: OPA2356AIDGKR; VSSOP-8_L3.0-W3.0-P0.65-LS5.0-BL
U3: CH32V003F4P6; TSSOP-20_L6.5-W4.4-P0.65-LS6.4-BL
U4: TLV3501AIDBVR; SOT-23-6_L2.9-W1.6-P0.95-LS2.8-BR

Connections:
+3.3V: C3.1, C4.1, C5.1, C9.1, U1.5 (VOUT), U3.9 (VDD)
+5V: C1.1, C2.1, C6.1, CN1.1, CN2.1, Mux_x1.13 (VDD), Mux_y1.13 (VDD), R5.1, R8.2, U1.1 (VIN), U1.3 (EN), U2.8 (VS+), U4.4 (V+), U4.6 (SHDN)
/PD2 Pre: C11.1, D1.3 (A/C), R10.2, R11.2
D: C7.2, Mux_x1.8 (D), Mux_y1.8 (D), R1.2, U2.2 (INA-)
GND: C1.2, C2.2, C3.2, C4.2, C5.2, C6.2, C9.2, C10.2, CN1.2, CN2.2, JP1.1 (A), JP2.1 (A), JP3.1 (A), Mux_x1.3 (VSS), Mux_x1.14 (GND), Mux_y1.3 (VSS), Mux_y1.14 (GND), R6.2, TP1.2, TP2.2, U1.2 (GND), U2.4 (VS-), U3.7 (VSS), U4.2 (V-)
unnamed: J1.1 (Pin_1_1), U3.4 (PD7/NRST/T2CH4/OPP1/UCK_)
unnamed: J2.1 (Pin_1_1), Mux_x1.4 (S1)
unnamed: J3.1 (Pin_1_1), Mux_x1.5 (S2)
unnamed: J4.1 (Pin_1_1), Mux_x1.6 (S3)
unnamed: J5.1 (Pin_1_1), Mux_x1.7 (S4)
unnamed: J6.1 (Pin_1_1), Mux_x1.12 (S5)
unnamed: J7.1 (Pin_1_1), Mux_x1.11 (S6)
unnamed: J8.1 (Pin_1_1), Mux_x1.10 (S7)
unnamed: J9.1 (Pin_1_1), Mux_x1.9 (S8)
unnamed: J10.1 (Pin_1_1), Mux_y1.4 (S1)
unnamed: J11.1 (Pin_1_1), Mux_y1.5 (S2)
unnamed: J12.1 (Pin_1_1), Mux_y1.6 (S3)
unnamed: J13.1 (Pin_1_1), Mux_y1.7 (S4)
unnamed: J14.1 (Pin_1_1), Mux_y1.12 (S5)
unnamed: J15.1 (Pin_1_1), Mux_y1.11 (S6)
unnamed: J16.1 (Pin_1_1), Mux_y1.10 (S7)
unnamed: J17.1 (Pin_1_1), Mux_y1.9 (S8)
unnamed: J18.1 (Pin_1_1), U3.18 (PD1/SWIO/AETR2/T1CH3N/SCL_/URX_)
unnamed: JP1.2 (B), U3.1 (PD4/A7/UCK/T2CH1ETR/OPO/T1CH4ETR_)
unnamed: JP2.2 (B), U3.2 (PD5/A5/UTX/T2CH4_/URX_)
unnamed: JP3.2 (B), U3.3 (PD6/A6/URX/T2CH3_/UTX_)
unnamed: Q1.3 (D), R12.2
unnamed: C8.1, R2.2, U2.5 (INB+)
unnamed: R3.2, R4.1, U2.6 (INB-)
unnamed: TP6.1 (1_1), U3.5 (PA1/OSCI/A1/T1CH2/OPN0)
unnamed: R7.2, R8.1, TP4.1 (1_1), U4.1 (-IN)
unnamed: R9.1, U4.5 (OUT)
OUT_A: C7.1, C8.2, R1.1, TP1.1, U2.1 (OUTA)
OUT_B: D1.1 (A), R3.1, R12.1, TP2.1, U2.7 (OUTB), U4.3 (+IN)
PC0: Mux_x1.1 (A0), Mux_y1.1 (A0), U3.10 (PC0/T2CH3/UTX_/NSS_/T1CH3_)
PC3: Q1.1 (G), U3.13 (PC3/T1CH3/T1CH1N_/UCTS_)
PC4: Mux_x1.16 (A1), Mux_y1.16 (A1), U3.14 (PC4/A2/T1CH4/MCO/T1CH1CH2N_)
PC5: Mux_x1.15 (A2), Mux_y1.15 (A2), U3.15 (PC5/SCK/T1ETR/T2CH1ETR_/SCL_/UCK_/T1CH3_)
PC6: Mux_x1.2 (EN), U3.16 (PC6/MOSI/T1CH1CH3N_/UCTS_/SDA_)
PC7: Mux_y1.2 (EN), U3.17 (PC7/MISO/T1CH2_/T2CH2_/URTS_)
PD2: R11.1, U3.19 (PD2/A3/T1CH1/T2CH3_/T1CH2N_)
PD3: R9.2, TP5.1 (1_1), U3.20 (PD3/A4/T2CH2/AETR/UCTS/T1CH4_)
SCL: CN1.4, CN2.4, U3.12 (PC2/SCL/URTS/T1BKIN/AETR_/T2CH2_/T1ETR_)
SDA: CN1.3, CN2.3, U3.11 (PC1/SDA/NSS/T2CH4_/T2CH1ETR_/T1BKIN_/UR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)
v_half_ref: C10.1, C11.2, D1.2 (C), Q1.2 (S), R2.1, R4.2, R5.2, R6.1, R7.1, R10.1, TP3.1 (1_1), U2.3 (INA+)
